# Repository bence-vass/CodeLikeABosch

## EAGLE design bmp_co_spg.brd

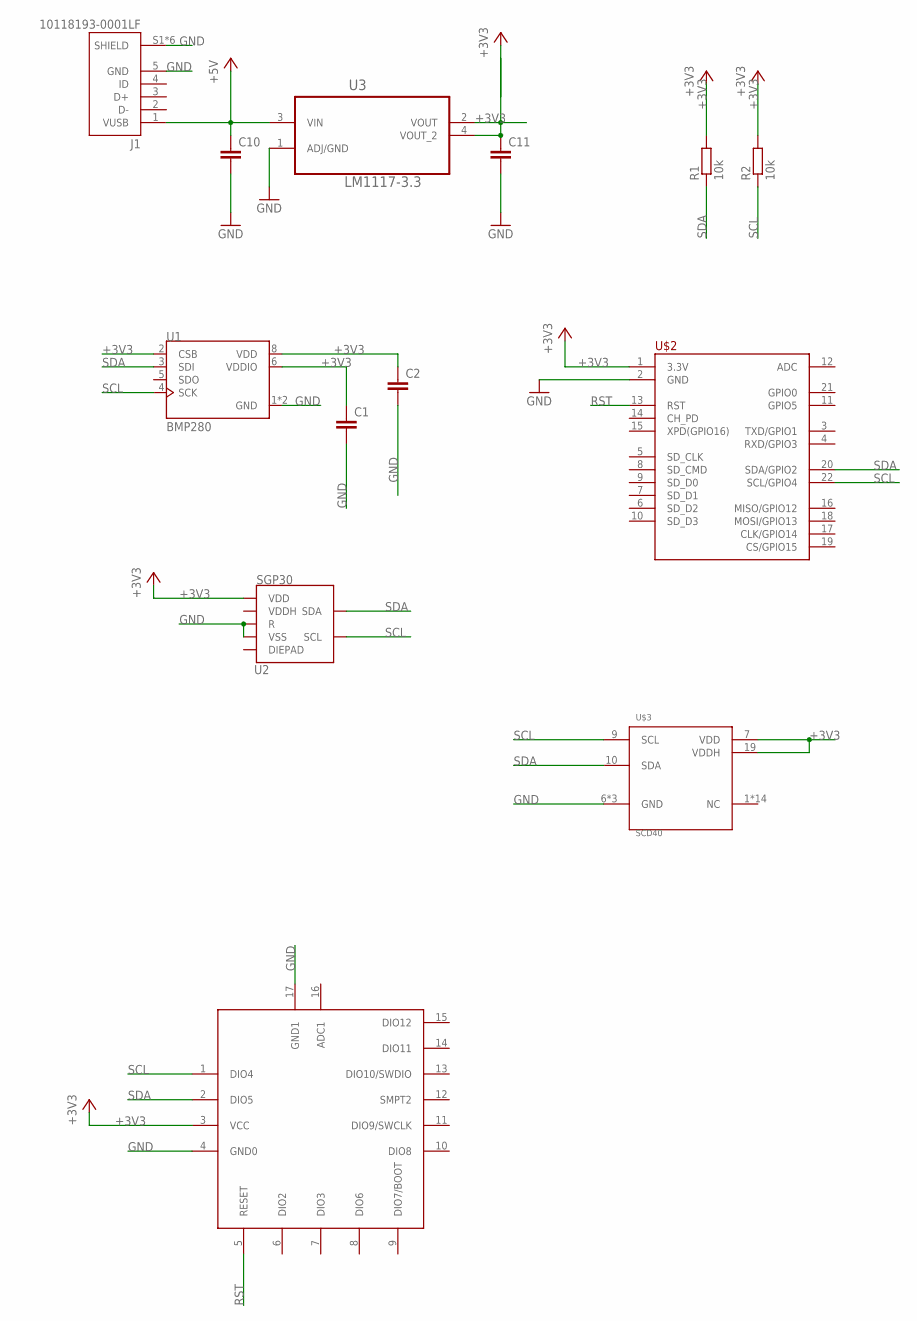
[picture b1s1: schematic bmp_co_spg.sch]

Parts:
C1, C2: 100nF; C1206
C10: 47u; C1206
C11: 10u; C1206
J1: 10118193-0001LF; FCI_10118193-0001LF
R1, R2: 10k; R0402
U1: BMP280; XDCR_BMP280
U2: SGP30
U3: LM1117-3.3; SOT230
U$1: BLUENRG-234BLEMODULE
U$2: OLIMEX_MOD-WIFI-ESP8266-DEV>PINS-OUTSIDE; OLIMEX_MOD-WIFI-ESP8266-DEV-PINS-OUTSIDE
U$3: SCD40; SCD4X

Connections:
+3V3: C1.1, C2.1, C11.1, R1.2, R2.2, U1.2 (CSB), U1.6 (VDDIO), U1.8 (VDD), U2.1 (VDD), U3.2 (VOUT), U3.4 (VOUT_2), U$1.3 (VCC), U$2.1 (3.3V), U$3.7 (VDD), U$3.19 (VDDH)
+5V: C10.1, J1.1 (VUSB), U3.3 (VIN)
GND: C1.2, C2.2, C10.2, C11.2, J1.5 (GND), J1.S1 (SHIELD), J1.S2 (SHIELD), J1.S3 (SHIELD), J1.S4 (SHIELD), J1.S5 (SHIELD), J1.S6 (SHIELD), U1.1 (GND), U1.7 (GND), U2.2 (VSS), U2.4 (R), U3.1 (ADJ/GND), U$1.4 (GND0), U$1.17 (GND1), U$2.2 (GND), U$3.6 (GND), U$3.20 (GND), U$3.21 (GND)
RST: U$1.5 (RESET), U$2.13 (RST)
SCL: R2.1, U1.4 (SCK), U2.6 (SCL), U$1.1 (DIO4), U$2.22 (SCL/GPIO4), U$3.9 (SCL)
SDA: R1.1, U1.3 (SDI), U2.3 (SDA), U$1.2 (DIO5), U$2.20 (SDA/GPIO2), U$3.10 (SDA)

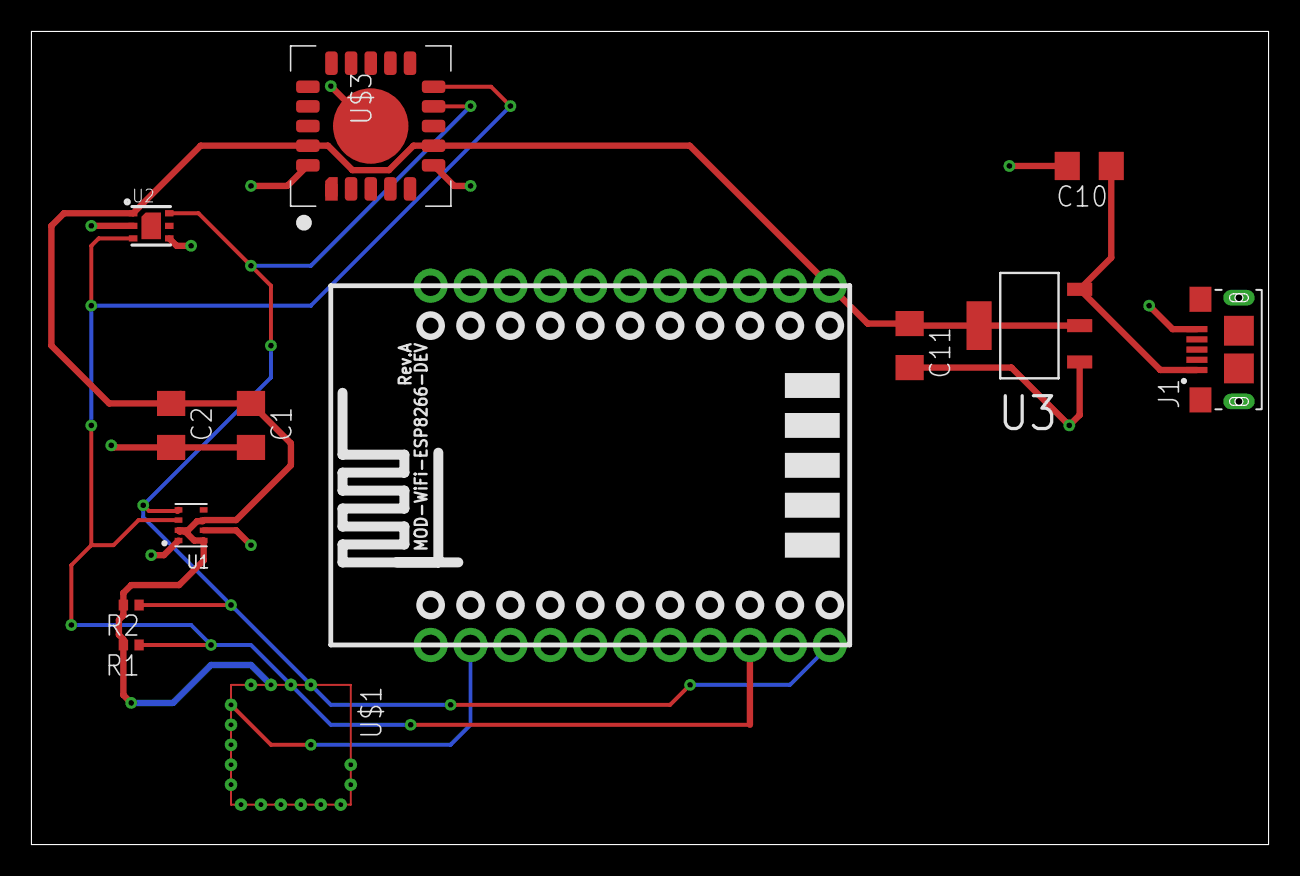
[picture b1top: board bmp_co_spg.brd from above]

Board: 2 copper layers, 78.7 x 51.7 mm, 13 parts (0 on the bottom side), 6 nets.

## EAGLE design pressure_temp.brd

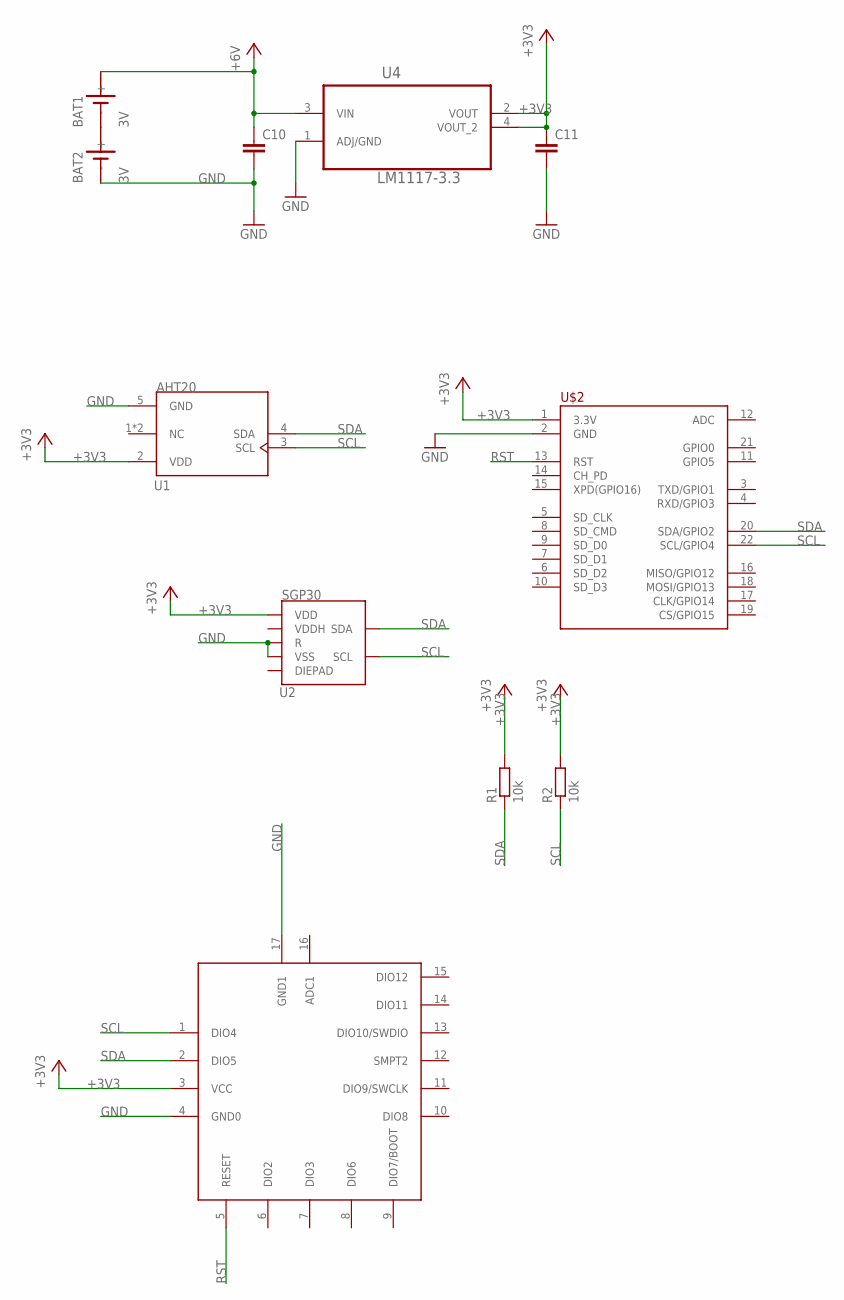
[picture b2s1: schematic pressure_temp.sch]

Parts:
BAT1, BAT2: 3V; SN2032
C10: 47u; C1206
C11: 10u; C1206
R1, R2: 10k; R0402
U1: AHT20; PSON100P300X300X110-6N
U2: SGP30
U4: LM1117-3.3; SOT230
U$1: BLUENRG-234BLEMODULE
U$2: OLIMEX_MOD-WIFI-ESP8266-DEV>PINS-OUTSIDE; OLIMEX_MOD-WIFI-ESP8266-DEV-PINS-OUTSIDE

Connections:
+3V3: C11.1, R1.2, R2.2, U1.2 (VDD), U2.1 (VDD), U4.2 (VOUT), U4.4 (VOUT_2), U$1.3 (VCC), U$2.1 (3.3V)
+6V: BAT1.+, C10.1, U4.3 (VIN)
GND: BAT2.-, C10.2, C11.2, U1.5 (GND), U2.2 (VSS), U2.4 (R), U4.1 (ADJ/GND), U$1.4 (GND0), U$1.17 (GND1), U$2.2 (GND)
unnamed: BAT1.-, BAT2.+
RST: U$1.5 (RESET), U$2.13 (RST)
SCL: R2.1, U1.3 (SCL), U2.6 (SCL), U$1.1 (DIO4), U$2.22 (SCL/GPIO4)
SDA: R1.1, U1.4 (SDA), U2.3 (SDA), U$1.2 (DIO5), U$2.20 (SDA/GPIO2)

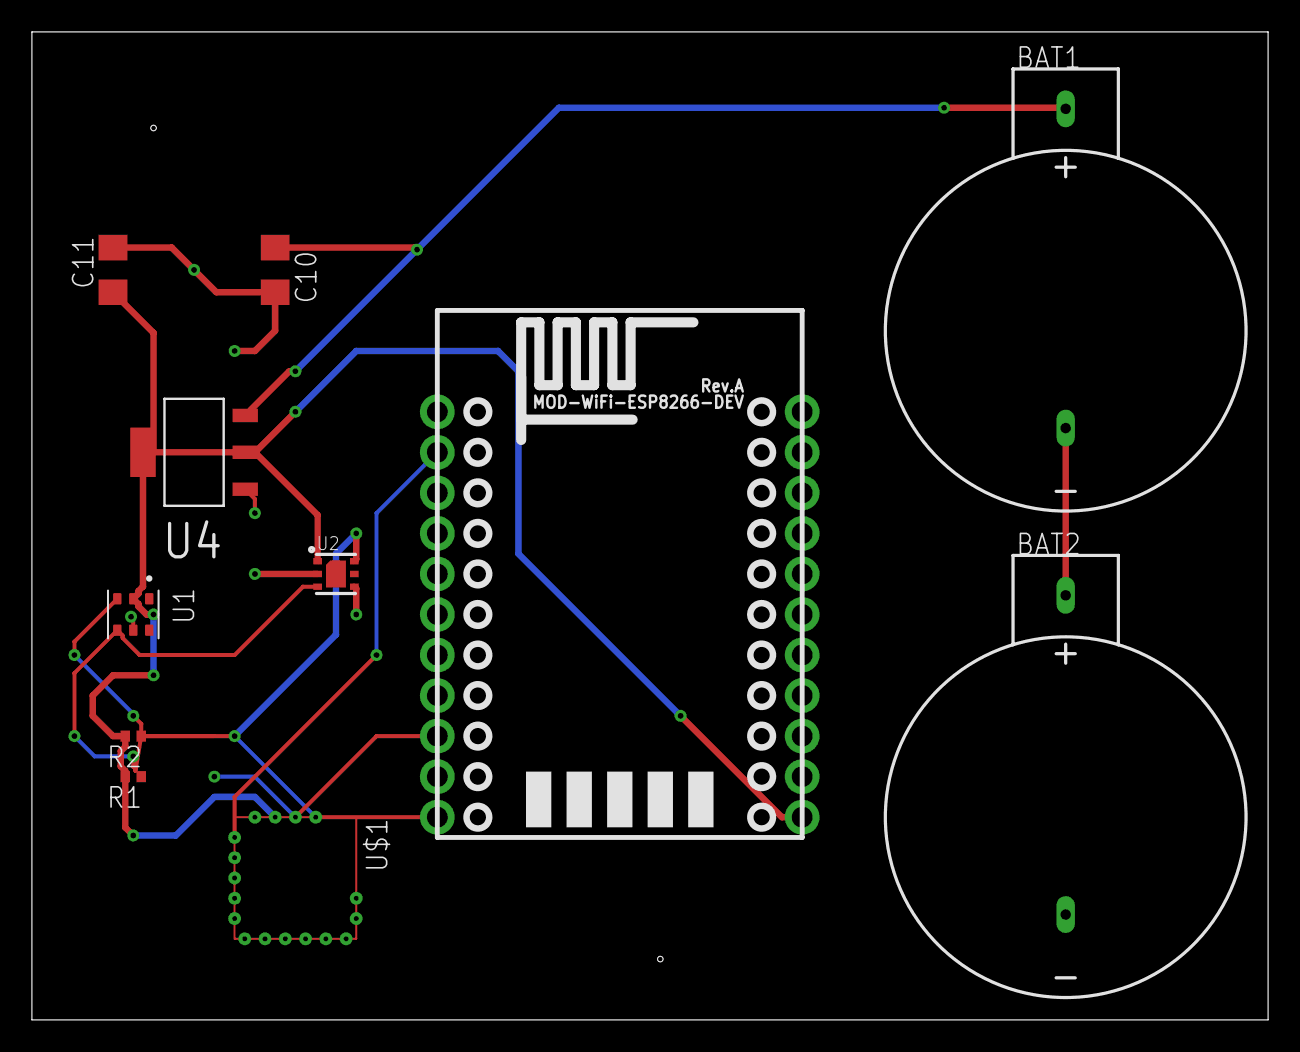
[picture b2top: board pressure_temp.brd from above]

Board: 2 copper layers, 77.5 x 61.9 mm, 11 parts (0 on the bottom side), 7 nets.

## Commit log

2022-10-02 init commit
